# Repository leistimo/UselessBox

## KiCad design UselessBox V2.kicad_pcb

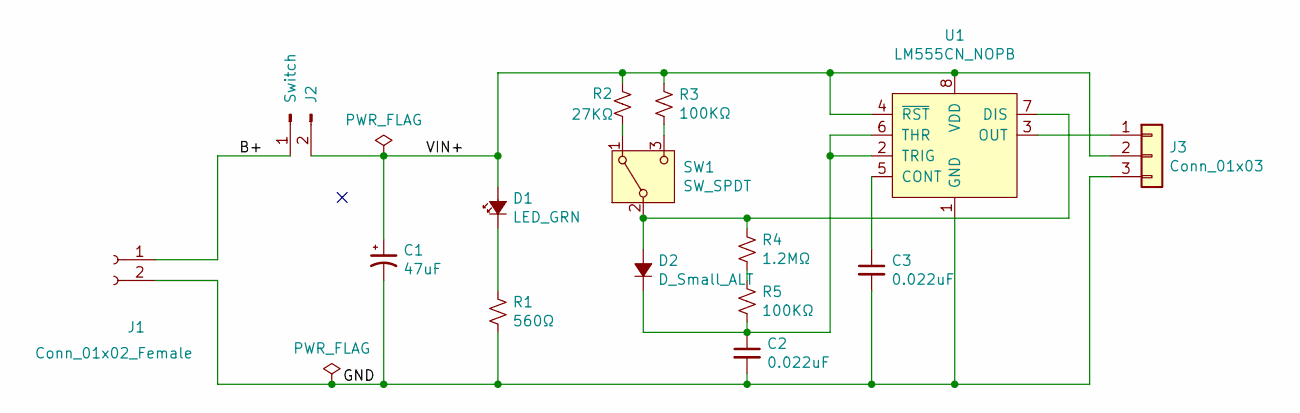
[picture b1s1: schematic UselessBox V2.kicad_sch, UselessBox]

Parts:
C1: 47uF; CP_Radial_D5.0mm_P2.00mm
C2, C3: 0.022uF; C_Rect_L4.0mm_W2.5mm_P2.50mm
D1: LED_GRN; LED_D3.0mm
D2: D_Small_ALT; D_DO-41_SOD81_P10.16mm_Horizontal
J1: Conn_01x02_Female; PinHeader_1x02_P2.54mm_Vertical
J2: Switch; JST_VH_B2P-VH-FB-B_1x02_P3.96mm_Vertical
J3: Conn_01x03; PinHeader_1x03_P2.54mm_Vertical
R1: 560Ω; R_Axial_DIN0207_L6.3mm_D2.5mm_P7.62mm_Horizontal
R2: 27KΩ; R_Axial_DIN0207_L6.3mm_D2.5mm_P7.62mm_Horizontal
R3, R5: 100KΩ; R_Axial_DIN0207_L6.3mm_D2.5mm_P7.62mm_Horizontal
R4: 1.2MΩ; R_Axial_DIN0207_L6.3mm_D2.5mm_P7.62mm_Horizontal
SW1: SW_SPDT; PinHeader_1x03_P2.54mm_Vertical
U1: LM555CN_NOPB; DIP-8_W7.62mm_LongPads; MPN LM555CN/NOPB; Digi-Key_PN LM555CNNS/NOPB-ND

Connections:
/B+: J1.1, J2.1
/GND: C1.2, C2.2, C3.2, J1.2, J3.3, R1.2, U1.1 (GND)
/VIN+: C1.1, D1.2 (A), J2.2, J3.2, R2.1, R3.1, U1.4 (~RST), U1.8 (VDD)
unnamed: D1.1 (K), R1.1
unnamed: D2.2 (A), R4.1, SW1.2 (B), U1.7 (DIS)
unnamed: C2.1, D2.1 (K), R5.2, U1.2 (TRIG), U1.6 (THR)
unnamed: J3.1, U1.3 (OUT)
unnamed: R4.2, R5.1
unnamed: R2.2, SW1.1 (A)
unnamed: R3.2, SW1.3 (C)
unnamed: C3.1, U1.5 (CONT)

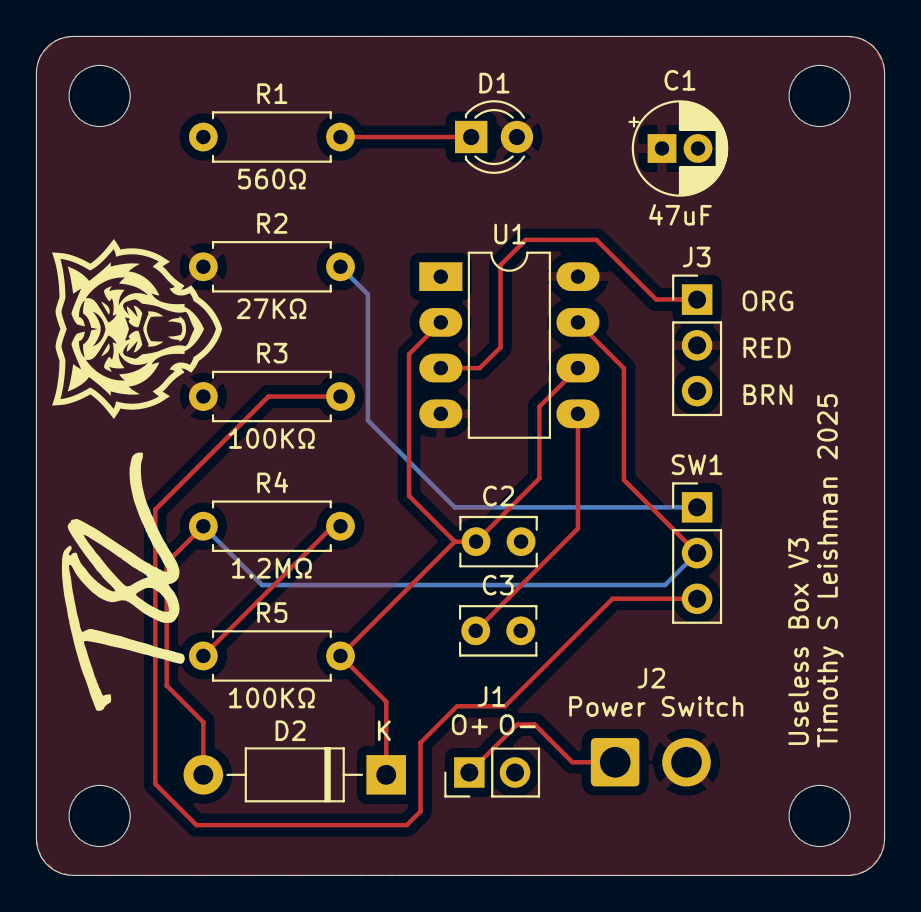
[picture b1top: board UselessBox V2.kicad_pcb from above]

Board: 2 copper layers, 47.1 x 46.6 mm, 15 parts (0 on the bottom side), 11 nets.

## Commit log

2022-04-12 added github silkscreen to pcb
2022-04-12 corrected SERVO pinout
2022-04-12 added logos
2022-04-12 final touches
2022-04-13 Gerber Files
2022-04-18 STL files designing box
2022-04-25 corrected power switch location
2022-04-26 stl file done for base and arm also revised PCB switch
2022-04-26 Corrected ground problem and generated Gerbers
2022-05-05 modified STL arm and base file
2022-05-06 added video
2023-01-20 1-20-23
2024-12-20 Uselessbox 9V ver
2024-12-20 Version 3
